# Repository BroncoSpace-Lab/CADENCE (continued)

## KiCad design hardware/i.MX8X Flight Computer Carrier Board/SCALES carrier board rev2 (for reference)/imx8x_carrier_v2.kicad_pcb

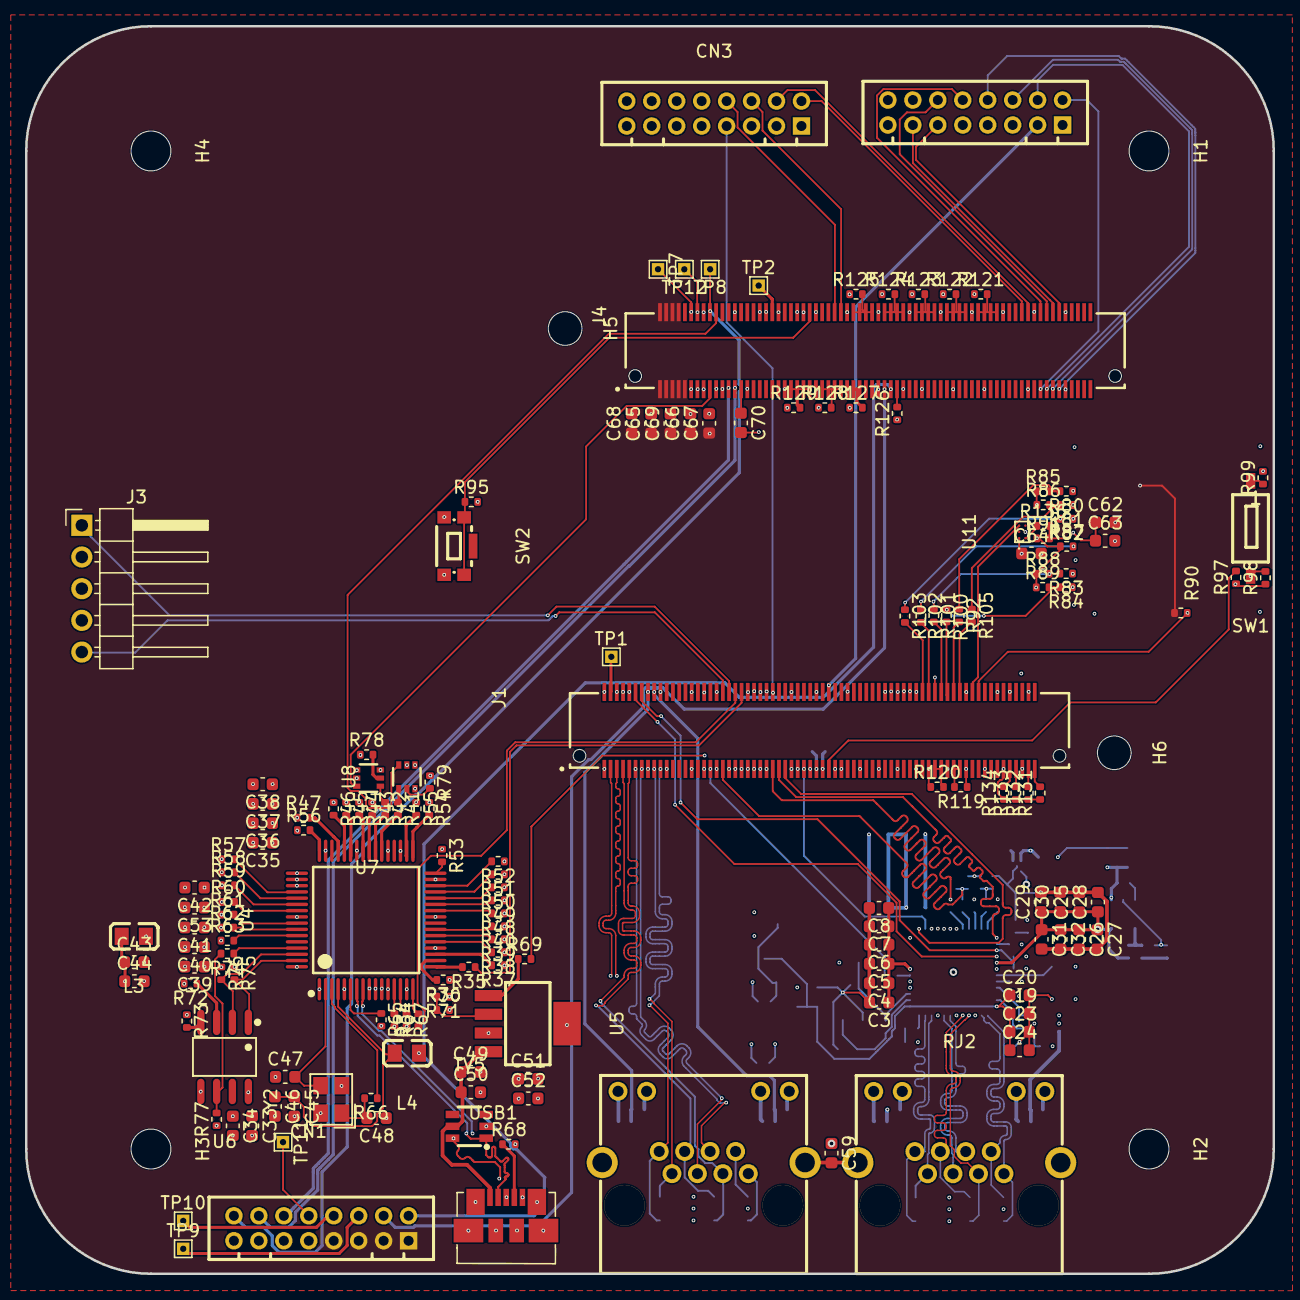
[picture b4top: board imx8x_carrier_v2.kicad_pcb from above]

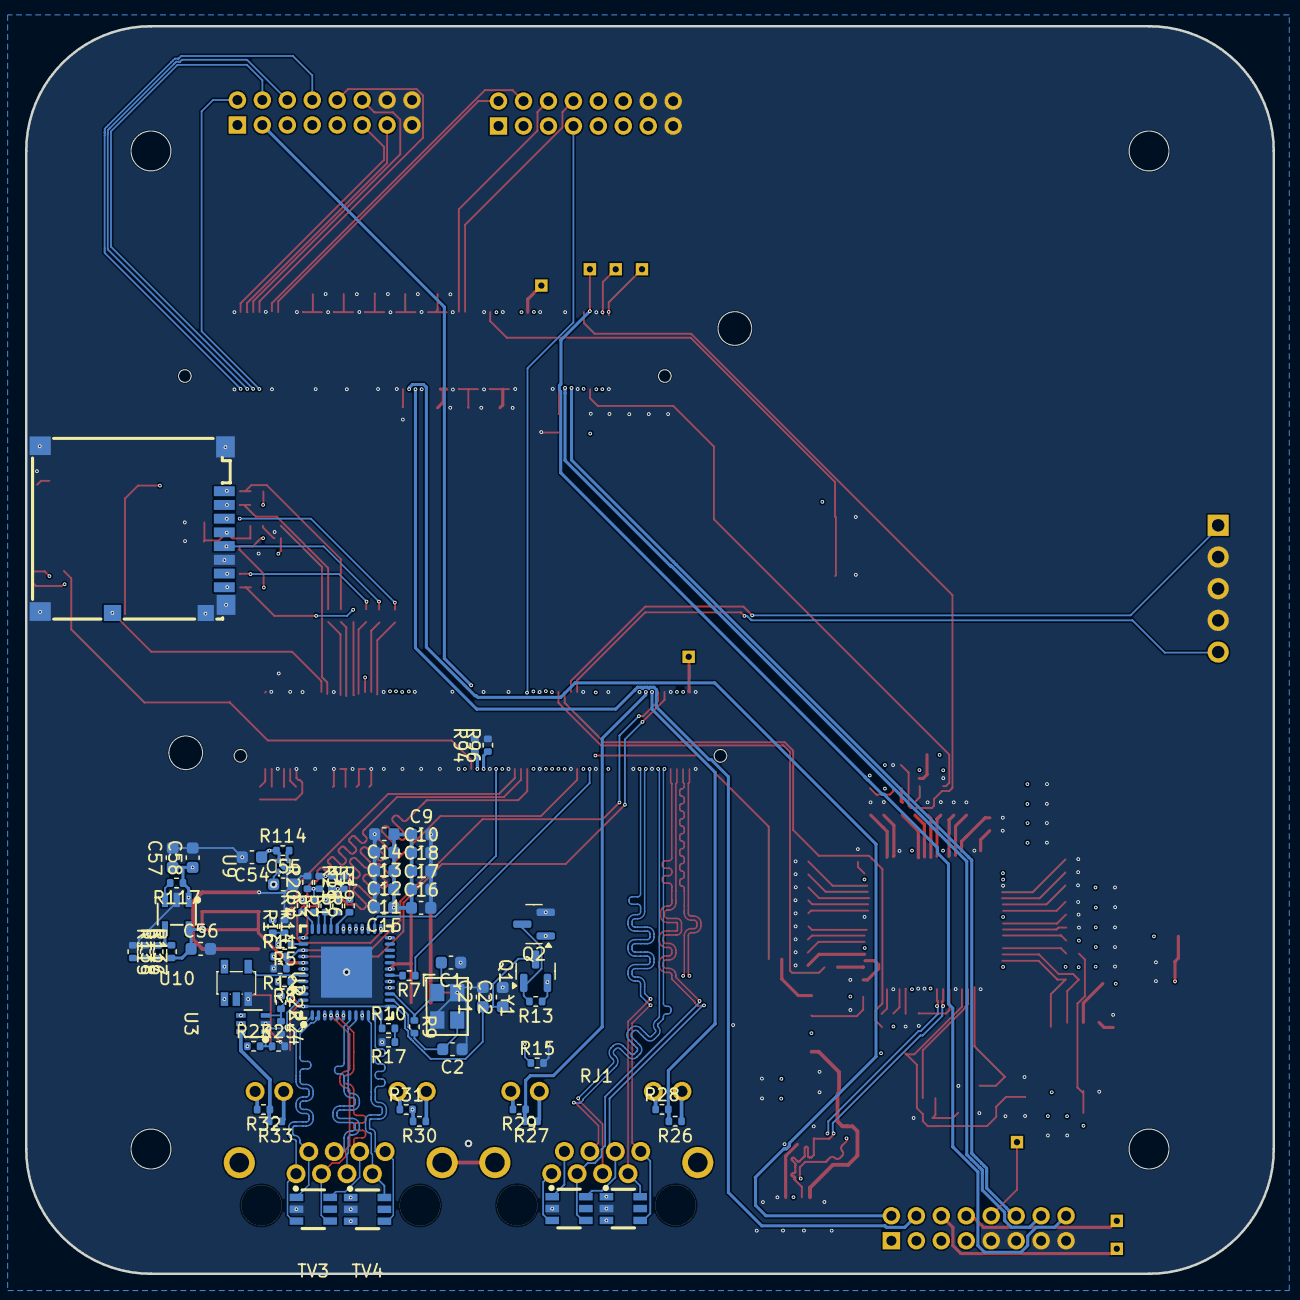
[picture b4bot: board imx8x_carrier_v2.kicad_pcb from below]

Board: 6 copper layers, 100.0 x 100.0 mm, 241 parts (73 on the bottom side), 215 nets.

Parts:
C1, C2: 18pF; C_0603_1608Metric
C3, C5, C12, C14, C15, C17, C19, C24, C25, C27, C32, C51: 1uF; C_0603_1608Metric
C4, C6, C11, C13, C16, C18, C20, C23, C26, C28, C31, C34, C35, C36, C37, C39, C40, C41, C42, C43, C46, C49, C52, C53, C54, C55, C57, C63, C64, C69: 100nF; C_0603_1608Metric
C7, C10, C21, C29, C59: 10nF; C_0603_1608Metric
C8, C9, C22, C30, C62: 10uF; C_0603_1608Metric
C33, C38, C44, C45, C56, C58, C67, C68: 4.7uF; C_0603_1608Metric
C47, C48: 12pF; C_0603_1608Metric
C50: 2.2uF; C_0603_1608Metric
C65, C66: 22uF; C_0603_1608Metric
C70: 220nF; C_0603_1608Metric
CN1, CN2, CN3: DF11-16DP-2DSA(08); CONN-TH_DF11-16DP-2DSA-08
Card1: 5027740891; TF-SMD_5027740891
H1, H2, H3, H4: MountingHole; MountingHole_3.2mm_M3
H5, H6: MountingHole; MountingHole_2.7mm_M2.5
J1, J4: BTH-070-02-L-D-A; SAMTEC_BTH-070-02-L-D-A
J3: Conn_01x05_Pin; PinHeader_1x05_P2.54mm_Horizontal
L3, L4: 600R/100MHz; L0805
Q1: IRLML6401; SOT-23
Q2: BSS138; SOT-23
R1, R2, R3, R4, R5, R29, R32, R34, R35, R41, R42, R80, R81, R82, R83, R84, R92, R100, R101, R102, R103, R105: 22; R_0402_1005Metric
R6, R68, R73, R91, R136: 0; R_0402_1005Metric
R7: 49.9; R_0402_1005Metric
R8, R74, R95: 2K; R_0402_1005Metric
R9: 1M; R_0402_1005Metric
R10, R63, R67: 1K; R_0402_1005Metric
R11, R14, R23: 5.76K; R_0402_1005Metric
R12, R16, R19, R20, R21, R24, R25, R27, R33: 2.49K; R_0402_1005Metric
R13, R15, R17, R18, R22, R26, R30, R36, R37, R38, R39, R40, R43, R44, R45, R46, R47, R48, R49, R50, R51, R52, R53, R54, R55, R56, R57, R58, R59, R60, R61, R62, R64, R69, R70, R72, R75, R76, R77, R78, R79: 10K; R_0402_1005Metric
R28, R31, R66: 200; R_0402_1005Metric
R65: 12K; R_0402_1005Metric
R71: 16.5K; R_0402_1005Metric
R85, R86, R87, R88, R89, R90: 49.9K; R_0402_1005Metric
R94, R96, R97, R98, R99, R137, R138: 1k; R_0402_1005Metric
R114, R117, R119, R120, R121, R122, R123, R124, R125, R126, R127, R128, R129, R131, R132, R133, R134: 10k; R_0402_1005Metric
R115: 2k; R_0402_1005Metric
R116: 13k; R_0402_1005Metric
RJ1, RJ2: RJHSE5384; RJ45-TH_RJHSE5384
SW1: SW_DIP_x01; SW-SMD_1.27-1P-TPPT
SW2: KMR221GLFS; KEY-SMD_KMR2XXGXXX
TP1, TP2, TP7, TP8, TP9, TP10, TP11, TP12: TestPoint; TestPoint_THTPad_1.0x1.0mm_Drill0.5mm
TV1, TV2, TV3, TV4, TV5: SRV05-4.TCT; SOT-23-6_L2.9-W1.6-P0.95-LS2.8-BR
U1: DP83867IRRGZR; VQFN-48_L7.0-W7.0-P0.50-BL-EP4.1
U2: 74AUP1G08; SOT-23-5_L3.0-W1.7-P0.95-LS2.8-BR
U3: 74LVC2G07; SOT-363_L2.1-W1.3-P0.65-LS2.2-BL
U4: FT2232HL; LQFP-64_L10.0-W10.0-P0.50-LS12.0-TL
U5: LP38693MP-ADJ/NOPB; SOT-223-5_L6.5-W3.5-P1.50-LS7.0-BL
U6: CAT93C66VI-GT3; SOIC-8_L4.9-W3.9-P1.27-LS6.0-BL
U7, U8: TXS0101DCKR; SC-70-6_L2.0-W1.3-P0.65-LS2.1-BR
U9: TLV71310PDQNR; X2SON-4_L1.0-W1.0-P0.65-TL-EP
U10: MCP1824T-ADJE/OT; SOT-23-5_L3.0-W1.7-P0.95-LS2.8-BL
U11: BD2204GUL-E2; BGA-6_L1.5-W1.0-P0.50_BD2204GUL-E2
USB1: 47346-0001; MICRO-USB-SMD_47346-0001
Y1: 25MHz; CRYSTAL-SMD_4P-L3.2-W2.5-BL-2
Y2: 12MHz; CRYSTAL-SMD_4P-L3.2-W2.5-BL

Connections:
1V8_FTDI: C35.1, C36.1, C37.1, C38.1, U4.12 (VCORE), U4.37 (VCORE), U4.49 (VREGOUT), U4.64 (VCORE)
3V3_FTDI: C33.1, C34.1, C39.1, C40.1, C41.1, C42.1, C51.1, C52.1, C53.1, L3.1, L4.1, R63.1, R67.2, R71.1, R75.1, R76.1, R77.1, U4.20 (VCCIO), U4.31 (VCCIO), U4.42 (VCCIO), U4.50 (VREGIN), U4.56 (VCCIO), U5.3 (OUT), U6.8 (VCC)
/Debug USB - UART/DEBUG_USB_DN: TV5.1, U4.7 (DM), USB1.2 (Data-)
/Debug USB - UART/DEBUG_USB_DP: TV5.6, U4.8 (DP), USB1.3 (Data+)
/Debug USB - UART/DEBUG_USB_ID: R68.1, USB1.4 (ID)
/Debug USB - UART/FTDI_OSCI: C47.2, U4.2 (OSCI), Y2.3
/Debug USB - UART/FTDI_OSCO: C48.2, R66.2, Y2.1
/Debug USB - UART/M40_UART0_RX: R41.1, U8.4 (B)
/Debug USB - UART/M40_UART0_TX: R42.1, U7.4 (B)
ETH1_A_TX_N: RJ2.2, TV3.1, U1.2 (TD_M_A)
ETH1_A_TX_P: RJ2.1, TV3.3, U1.1 (TD_P_A)
ETH1_B_TX_N: RJ2.6, TV3.6, U1.5 (TD_M_B)
ETH1_B_TX_P: RJ2.3, TV3.4, U1.4 (TD_P_B)
ETH1_C_TXCLK_N: RJ2.5, TV4.3, U1.8 (TD_M_C)
ETH1_C_TXCLK_P: RJ2.4, TV4.1, U1.7 (TD_P_C)
ETH1_D_RXDV_N: RJ2.8, TV4.4, U1.11 (TD_M_D)
ETH1_D_RXDV_P: RJ2.7, TV4.6, U1.10 (TD_P_D)
ETH1_LED0: R32.1, R33.2, U3.6 (1Y)
ETH1_LED1: R30.2, R31.2, U3.4 (2Y)
GND: C1.1, C2.1, C3.2, C4.2, C5.2, C6.2, C7.2, C8.2, C9.2, C10.2, C11.2, C12.2, C13.2, C14.2, C15.2, C16.2, C17.2, C18.2, C19.2, C20.2, C21.2, C22.2, C23.2, C24.2, C25.2, C26.2, C27.2, C28.2, C29.2, C30.2, C31.2, C32.2, C33.2, C34.2, C35.2, C36.2, C37.2, C38.2, C39.2, C40.2, C41.2, C42.2, C43.2, C44.2, C45.2, C46.2, C47.1, C48.1, C49.2, C50.2, C51.2, C52.2, C53.2, C54.2, C55.2, C56.2, C57.2, C58.2, C59.1, C62.2, C63.2, C64.2, C65.2, C66.2, C67.2, C68.2, C69.2, C70.2, CN1.9, CN1.11, CN1.13, CN1.15, CN2.14, CN2.15, CN2.16, CN3.14, CN3.15, CN3.16, Card1.6 (VSS), Card1.10 (DET), Card1.11 (SHELL), Card1.12 (SHELL), Card1.13 (SHELL), Card1.14 (SHELL), J1.03 (A2), J1.06 (B3), J1.09 (A5), J1.12 (B6), J1.13 (A7), J1.18 (B9), J1.23 (A12), J1.24 (B12), J1.30 (B15), J1.36 (B18), J1.39 (A20), J1.40 (B20), J1.46 (B23), J1.49 (A25), J1.52 (B26), J1.58 (B29), J1.61 (A31), J1.64 (B32), J1.71 (A36), J1.74 (B37), J1.79 (A40), J1.80 (B40), J1.89 (A45), J1.90 (B45), J1.100 (B50), J1.103 (A52), J1.108 (B54), J1.111 (A56), J1.120 (B60), J1.121 (A61), J1.126 (B63), J1.131 (A66), J1.139 (A70), J1.140 (B70), J3.2, J3.3, J3.4, J4.09 (C5), J4.10 (D5), J4.19 (C10), J4.22 (D11), J4.29 (C15), J4.36 (D18), J4.39 (C20), J4.46 (D23), J4.49 (C25), J4.56 (D28), J4.59 (C30), J4.62 (D31), J4.69 (C35), J4.70 (D35), J4.79 (C40), J4.80 (D40), J4.89 (C45), J4.90 (D45), J4.95 (C48), J4.100 (D50), J4.107 (C54), J4.112 (D56), J4.115 (C58), J4.120 (D60), J4.125 (C63), J4.130 (D65), Q2.2 (S), R12.2, R15.2, R16.2, R17.2, R20.2, R21.2, R24.2, R25.2, R36.1, R37.1, R38.1, R39.1, R40.1, R43.1, R44.1, R45.1, R46.1, R47.1, R48.1, R49.1, R50.1, R51.1, R52.1, R53.1, R54.1, R55.1, R56.1, R57.1, R58.1, R59.1, R60.1, R61.1, R62.1, R64.2, R65.2, R68.2, R70.2, R73.1, R94.2, R96.2, R99.2, R119.1, R120.1, R121.1, R122.1, R123.1, R124.1, R125.1, R126.1, R127.1, R128.1, R129.1, R131.1, R132.1, R133.1, R134.1, R137.1, R138.1, SW2.3, SW2.4, TV1.2, TV2.2, TV3.2, TV4.2, TV5.2, U1.49 (GND), U2.3 (GND), U3.2 (GND), U4.1 (GND), U4.5 (GND), U4.10 (AGND), U4.11 (GND), U4.15 (GND), U4.25 (GND), U4.35 (GND), U4.47 (GND), U4.51 (GND), U5.5 (GND), U6.5 (GND), U7.2 (GND), U8.2 (GND), U9.2 (GND), U9.5 (PAD), U10.2 (GND), U11.B2 (GND), USB1.5 (GND), USB1.6, Y1.2, Y1.4, Y2.2, Y2.4
GNDPWR: C59.2, RJ1.13 (SHELL), RJ1.14 (SHELL), RJ2.13 (SHELL), RJ2.14 (SHELL)
LED0_LINK: R23.2, R25.1, U1.47 (LED_0), U3.1 (1A)
LED2_ACT: R22.2, R24.1, U1.45 (LED_2), U3.3 (2A)
unnamed: CN1.6, TP9.1
unnamed: CN1.8, TP10.1
unnamed: CN1.10, TP11.1
unnamed: Card1.2 (CD/DAT3), R81.1
unnamed: Card1.3 (CMD), R82.1
unnamed: Card1.7 (DAT0), R83.1
unnamed: Card1.8 (DAT1), R84.1
unnamed: Card1.1 (DAT2), R80.1
unnamed: C62.1, C63.1, Card1.4 (VDD), R91.2, R136.2
unnamed: J1.25 (A13), R105.2
unnamed: J1.27 (A14), R92.2
unnamed: J1.29 (A15), R100.2
unnamed: J1.31 (A16), R101.2
unnamed: J1.35 (A18), R102.2
unnamed: J1.37 (A19), R103.2
unnamed: J1.02 (B1), R131.2
unnamed: J1.04 (B2), R132.2
unnamed: J1.08 (B4), R133.2
unnamed: J1.10 (B5), R134.2
unnamed: J1.26 (B13), J1.28 (B14), R119.2
unnamed: J1.32 (B16), J1.34 (B17), R120.2
unnamed: J4.31 (C16), J4.33 (C17), J4.35 (C18), J4.37 (C19), R121.2
unnamed: J4.41 (C21), J4.43 (C22), J4.45 (C23), J4.47 (C24), R122.2
unnamed: J4.51 (C26), J4.53 (C27), J4.55 (C28), J4.57 (C29), R123.2
unnamed: J4.61 (C31), J4.63 (C32), J4.65 (C33), J4.67 (C34), R124.2
unnamed: J4.71 (C36), J4.73 (C37), J4.75 (C38), J4.77 (C39), R125.2
unnamed: J4.64 (D32), R126.2
unnamed: J4.76 (D38), J4.78 (D39), R127.2
unnamed: J4.82 (D41), J4.84 (D42), J4.86 (D43), J4.88 (D44), R128.2
unnamed: J4.92 (D46), J4.94 (D47), J4.96 (D48), J4.98 (D49), R129.2
unnamed: C19.1, C20.1, C21.1, C22.1, C23.1, C24.1, Q1.3 (D), U1.13 (VDDA1P8), U1.48 (VDDA1P8)
unnamed: Q1.1 (G), Q2.3 (D), R13.2
unnamed: R10.2, R17.1
unnamed: R99.1, SW1.1
unnamed: R115.1, R137.2, R138.2
unnamed: R29.2, RJ1.9 (L-)
unnamed: R28.1, RJ1.11 (R-)
unnamed: R32.2, RJ2.9 (L-)
unnamed: R31.1, RJ2.11 (R-)
unnamed: R7.2, U1.18 (CLK_OUT)
unnamed: R10.1, U1.12 (RBIAS)
unnamed: U1.43 (RESET_N), U2.4 (Y)
unnamed: R6.1, U1.32 (RX_CLK)
unnamed: R5.1, U1.38 (RX_CTRL)
unnamed: R1.1, U1.33 (RX_D0)
unnamed: R2.1, U1.34 (RX_D1)
unnamed: R3.1, U1.35 (RX_D2)
unnamed: R4.1, U1.36 (RX_D3)
unnamed: C1.2, R9.1, U1.15 (X_I), Y1.1
unnamed: C2.2, R9.2, U1.14 (X_O), Y1.3
unnamed: R48.2, U4.26 (ACBUS0)
unnamed: R49.2, U4.27 (ACBUS1)
unnamed: R50.2, U4.28 (ACBUS2)
unnamed: R51.2, U4.29 (ACBUS3)
unnamed: R52.2, U4.30 (ACBUS4)
unnamed: R53.2, U4.32 (ACBUS5)
unnamed: R54.2, U4.33 (ACBUS6)
unnamed: R55.2, U4.34 (ACBUS7)
unnamed: R34.2, U4.16 (ADBUS0)
unnamed: R35.2, U4.17 (ADBUS1)
unnamed: R36.2, U4.18 (ADBUS2)
unnamed: R37.2, U4.19 (ADBUS3)
unnamed: R38.2, U4.21 (ADBUS4)
unnamed: R39.2, U4.22 (ADBUS5)
unnamed: R40.2, U4.23 (ADBUS6)
unnamed: R56.2, U4.48 (BCBUS0)
unnamed: R57.2, U4.52 (BCBUS1)
unnamed: R58.2, U4.53 (BCBUS2)
unnamed: R59.2, U4.54 (BCBUS3)
unnamed: R60.2, U4.55 (BCBUS4)
unnamed: R61.2, U4.57 (BCBUS5)
unnamed: R62.2, U4.58 (BCBUS6)
unnamed: R63.2, U4.59 (BCBUS7)
unnamed: R41.2, U4.38 (BDBUS0)
unnamed: R42.2, U4.39 (BDBUS1)
unnamed: R43.2, U4.40 (BDBUS2)
unnamed: R44.2, U4.41 (BDBUS3)
unnamed: R45.2, U4.43 (BDBUS4)
unnamed: R46.2, U4.44 (BDBUS5)
unnamed: R47.2, U4.45 (BDBUS6)
unnamed: R76.2, U4.62 (EECLK), U6.2 (SK)
unnamed: R75.2, U4.63 (EECS), U6.1 (CS)
unnamed: R74.1, U4.61 (EEDATA)
unnamed: R66.1, U4.3 (OSCO)
unnamed: R65.1, U4.6 (REF)
unnamed: R64.1, U4.13 (TEST)
unnamed: C45.1, C46.1, L4.2, U4.4 (VPHY)
unnamed: C43.1, C44.1, L3.2, U4.9 (VPLL)
unnamed: R67.1, U4.14 (~RESET)
unnamed: R70.1, R71.2, U5.2 (ADJ)
unnamed: R69.1, U5.1 (EN)
unnamed: R72.1, U6.3 (DI)
unnamed: R73.2, U6.4 (DO)
unnamed: R74.2, R77.2, U6.6 (ORG)
unnamed: R78.2, U7.5 (OE)
unnamed: R79.2, U8.5 (OE)
unnamed: R114.2, U9.3 (EN)
unnamed: R115.2, R116.2, U10.4 (ADJ)
unnamed: R117.2, U10.3 (EN)
SD1_SPWR: R136.1, U11.B1 (VOUT)
VBUS_DEBUG_USB: C49.1, C50.1, TV5.5, U5.4 (IN), USB1.1 (VBUS)
VCC_1V8_OUT: C54.1, J4.127 (C64), R11.1, R14.1, R18.1, R19.1, R22.1, R23.1, R78.1, R79.1, R114.1, TP12.1, U2.5 (VCC), U3.5 (VCC), U7.1 (VCCA), U8.1 (VCCA), U9.4 (IN)
VCC_3V3: C65.1, C66.1, C67.1, C68.1, C69.1, CN1.1, CN1.3, CN1.5, CN1.7, J4.132 (D66), J4.133 (C67), J4.134 (D67), J4.135 (C68), J4.136 (D68), J4.137 (C69), J4.138 (D69), J4.139 (C70), J4.140 (D70), R90.1
VCC_3V3_OUT: C57.1, C58.1, C64.1, J4.129 (C65), R8.2, R26.1, R27.1, R30.1, R33.1, R72.2, R95.2, R117.1, RJ1.10 (L+), RJ1.12 (R+), RJ2.10 (L+), RJ2.12 (R+), TP7.1, U7.6 (VCCB), U8.6 (VCCB), U10.1 (VIN), U11.A1 (VIN1)
VCC_ENET_2V5: C3.1, C4.1, C5.1, C6.1, C7.1, C8.1, C25.1, C26.1, C27.1, C28.1, C29.1, C30.1, C31.1, C32.1, C56.1, Q2.1 (G), R15.1, R116.1, U1.3 (VDDA2P5), U1.9 (VDDA2P5), U1.19 (VDDIO), U1.30 (VDDIO), U1.41 (VDDIO), U10.5 (OUT)
VCC_LDO_SD1: J1.33 (A17), R85.1, R86.1, R87.1, R88.1, R89.1, R91.1
VCC_SCU_1V8: J4.93 (C47), R97.1, R98.1
VDD_ADC_1V8: C70.1, J4.114 (D57)
VDD_ETH_1V0: C9.1, C10.1, C11.1, C12.1, C13.1, C14.1, C15.1, C16.1, C17.1, C18.1, C55.1, Q1.2 (S), R13.1, U1.6 (VDD1P0), U1.24 (VDD1P0), U1.31 (VDD1P0), U1.42 (VDD1P0), U9.1 (OUT)
X_ADMA_I2C0_SCL: CN1.2, J4.66 (D33)
X_ADMA_I2C0_SDA: CN1.4, J4.68 (D34)
X_ADMA_I2C3_SCL: CN3.10, J1.112 (B56)
X_ADMA_I2C3_SDA: CN3.12, J1.107 (A54)
X_ADMA_SPI2_CS0: CN2.1, J1.41 (A21)
X_ADMA_SPI2_CS1: CN2.3, J1.67 (A34)
X_ADMA_SPI2_SCK: CN2.5, J1.43 (A22)
X_ADMA_SPI2_SDI: CN2.7, J1.45 (A23)
X_ADMA_SPI2_SDO: CN2.9, J1.47 (A24)
X_ADMA_UART0_RX: J1.97 (A49), R34.1
X_ADMA_UART0_TX: J1.95 (A48), R35.1
X_ADMA_UART2_RX: J1.99 (A50), J3.1
X_ADMA_UART2_TX: J1.101 (A51), J3.5
X_BOOT_MODE0: J1.66 (B33), R98.2, SW1.2
X_BOOT_MODE1: J1.68 (B34), R97.2
X_BOOT_MODE2: J1.70 (B35), R94.1
X_BOOT_MODE3: J1.72 (B36), R96.1
X_CONN_ENET1_REFCLK: J1.106 (B53), R7.1
X_CONN_ENET1_RXC: J1.86 (B43), R6.2
X_CONN_ENET1_RXD0: J1.102 (B51), R1.2, R19.2, R21.1
X_CONN_ENET1_RXD1: J1.94 (B47), R2.2
X_CONN_ENET1_RXD2: J1.92 (B46), R3.2, R18.2, R20.1
X_CONN_ENET1_RXD3: J1.88 (B44), R4.2
X_CONN_ENET1_RX_CTL: J1.104 (B52), R5.2
X_CONN_ENET1_RX_CTRL: R14.2, R16.1
X_CONN_ENET1_TXC: J1.78 (B39), U1.29 (GTX_CLK)
X_CONN_ENET1_TXD0: J1.96 (B48), U1.28 (TX_D0)
X_CONN_ENET1_TXD1: J1.98 (B49), U1.27 (TX_D1)
X_CONN_ENET1_TXD2: J1.76 (B38), U1.26 (TX_D2)
X_CONN_ENET1_TXD3: J1.82 (B41), U1.25 (TX_D3)
X_CONN_ENET1_TX_CTL: J1.84 (B42), U1.37 (TX_CTRL)
X_CONN_ETH0_MDC: J1.135 (A68), U1.16 (MDC)
X_CONN_ETH0_MDIO: J1.133 (A67), U1.17 (MDIO)
X_CONN_ETH1_PHY_INT: R8.1, U1.44 (INT/PWDN)
X_CONN_USDHC1_CD_B: Card1.9 (SW), J1.19 (A10), R90.2
X_CONN_USDHC1_CLK: Card1.5 (CLK), R87.2, R102.1
X_CONN_USDHC1_CMD: R82.2, R103.1
X_CONN_USDHC1_DATA0: R83.2, R88.2, R101.1
X_CONN_USDHC1_DATA1: R84.2, R89.2, R100.1
X_CONN_USDHC1_DATA2: R80.2, R85.2, R92.1
X_CONN_USDHC1_DATA3: R81.2, R86.2, R105.1
X_CONN_USDHC1_RESET_B: J1.21 (A11), U11.A3 (EN)
X_ETH0_A_TX_N: J1.136 (B68), RJ1.2, TV1.1
X_ETH0_A_TX_P: J1.138 (B69), RJ1.1, TV1.3
X_ETH0_B_TX_N: J1.132 (B66), RJ1.6, TV1.6
X_ETH0_B_TX_P: J1.134 (B67), RJ1.3, TV1.4
X_ETH0_C_TXCLK_N: J1.128 (B64), RJ1.5, TV2.3
X_ETH0_C_TXCLK_P: J1.130 (B65), RJ1.4, TV2.1
X_ETH0_D_RXDV_N: J1.122 (B61), RJ1.8, TV2.4
X_ETH0_D_RXDV_P: J1.124 (B62), RJ1.7, TV2.6
X_ETH0_INT: J1.137 (A69), TP1.1
X_ETH0_LED0: J1.123 (A62), R27.2, R29.1
X_ETH0_LED1: J1.125 (A63), R26.2, R28.2
X_ETH_GPIO0: J1.127 (A64), R11.2, R12.1, U1.39 (GPIO_0)
X_ETH_GPIO1: J1.129 (A65), U1.40 (GPIO_1)
X_LSIO_GPIO1_IO09: CN1.14, J4.116 (D58)
X_LSIO_GPIO1_IO10: CN1.12, J4.118 (D59)
X_LSIO_GPIO1_IO12: CN3.1, J4.126 (D63)
X_LSIO_GPIO1_IO13: CN3.3, J4.128 (D64)
X_LSIO_GPIO1_IO14: CN3.5, J4.122 (D61)
X_LSIO_GPIO1_IO25: CN3.2, J4.23 (C12)
X_LSIO_GPIO1_IO26: CN3.4, J4.21 (C11)
X_LSIO_GPIO1_IO29: CN3.6, J4.81 (C41)
X_LSIO_GPIO1_IO30: CN3.8, J4.83 (C42)
X_LSIO_QSPI0B_DATA0: CN2.8, J4.12 (D6)
X_LSIO_QSPI0B_DATA1: CN2.6, J4.14 (D7)
X_LSIO_QSPI0B_DATA2: CN2.4, J4.16 (D8)
X_LSIO_QSPI0B_DATA3: CN2.2, J4.18 (D9)
X_LSIO_QSPI0B_DQS: CN2.10, J4.17 (C9)
X_LSIO_QSPI0B_SCLK: CN2.12, J4.15 (C8)
X_LSIO_QSPIOB_SS0_B: CN2.11, J4.11 (C6)
X_LSIO_QSPIOB_SS1_B: CN2.13, J4.13 (C7)
X_LSO_GPIO1_IO17: CN3.7, J1.85 (A43)
X_LSO_GPIO1_IO18: CN3.9, J1.87 (A44)
X_LSO_GPIO1_IO19: CN3.11, J1.93 (A47)
X_LSO_GPIO1_IO20: CN3.13, J1.91 (A46)
X_M40_UART0_RX: J4.121 (C61), U8.3 (A)
X_M40_UART0_TX: J4.124 (D62), U7.3 (A)
X_PGOOD: J4.105 (C53), R69.2
X_POR_B_1V8: J4.101 (C51), U2.1 (A)
X_POR_B_3V3: J4.103 (C52), TP2.1
X_SCU_WDOG0_WDOG_OUT: CN1.16, J4.123 (C62), TP8.1
~X_nRESET_IN: J4.91 (C46), R95.1, SW2.1, SW2.2

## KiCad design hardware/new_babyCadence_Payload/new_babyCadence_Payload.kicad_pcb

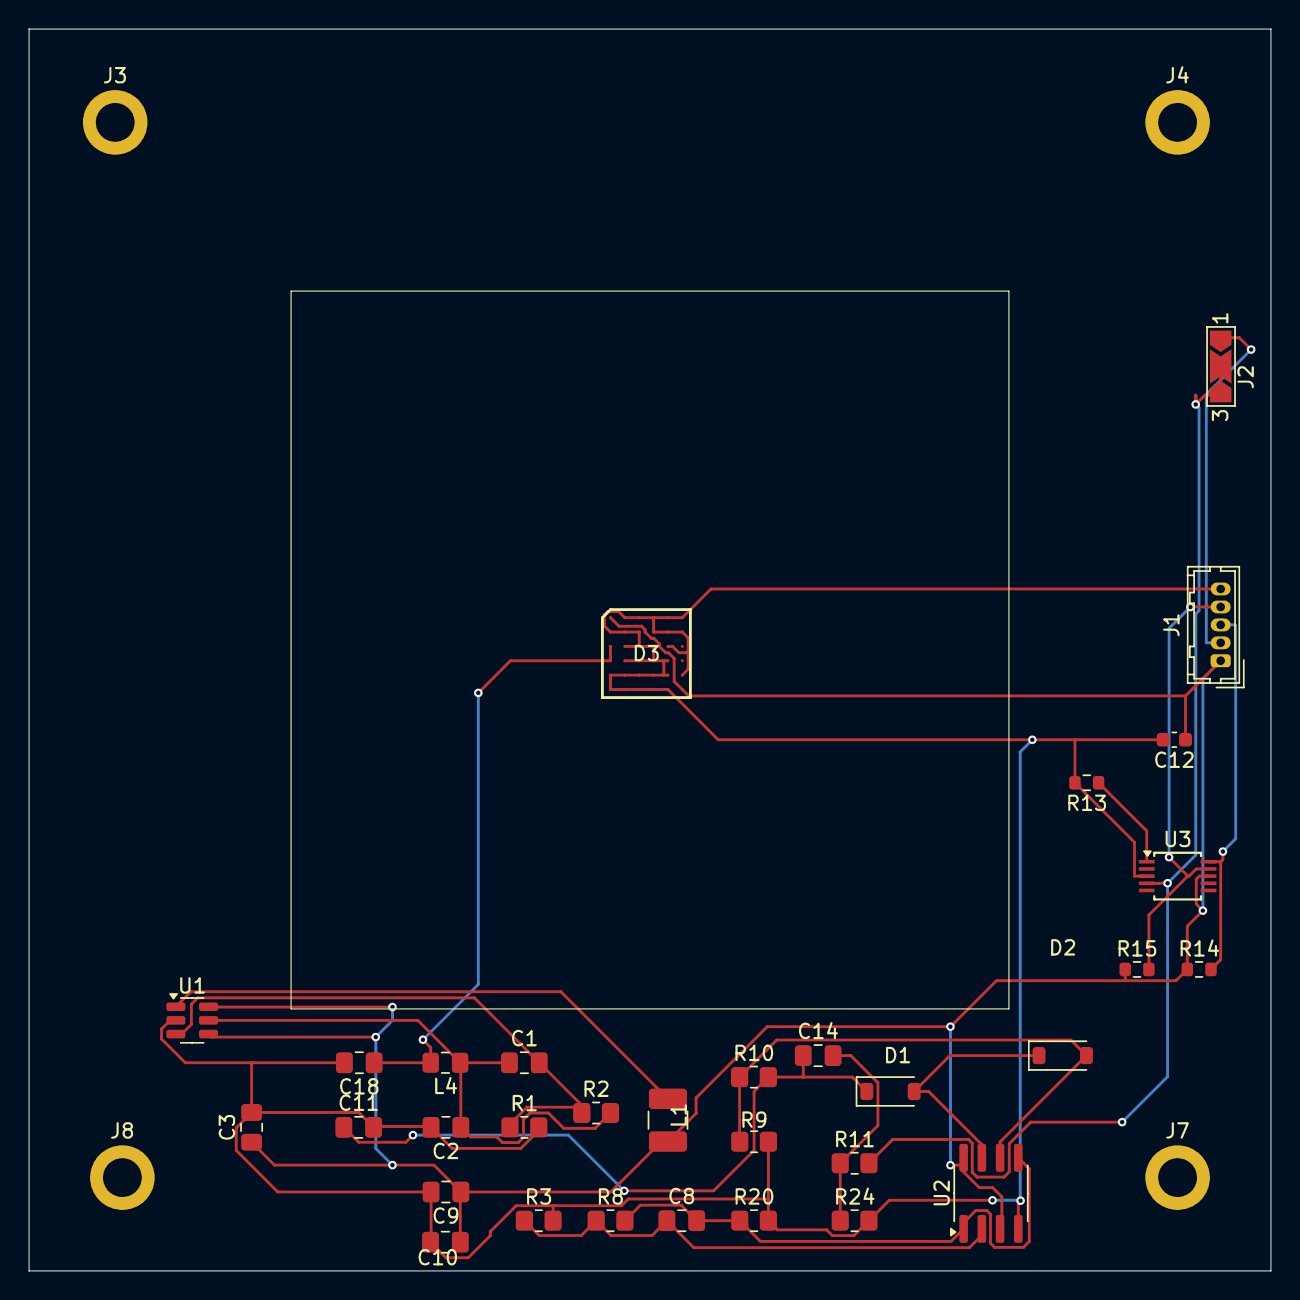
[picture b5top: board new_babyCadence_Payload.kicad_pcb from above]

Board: 2 copper layers, 86.5 x 86.5 mm, 36 parts (0 on the bottom side), 17 nets.

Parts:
C1: 22pF; C_0805_2012Metric_Pad1.18x1.45mm_HandSolder
C2: 0.47pF; C_0805_2012Metric_Pad1.18x1.45mm_HandSolder
C3, C18: 1uF; C_0805_2012Metric_Pad1.18x1.45mm_HandSolder
C8: 10pF; C_0805_2012Metric_Pad1.18x1.45mm_HandSolder
C9: 10uF; C_0805_2012Metric_Pad1.18x1.45mm_HandSolder
C10: 0.1uF; C_0805_2012Metric_Pad1.18x1.45mm_HandSolder
C11: 20nF; C_0805_2012Metric_Pad1.18x1.45mm_HandSolder
C12: 0.1; C_0603_1608Metric
C14: 0F; C_0805_2012Metric_Pad1.18x1.45mm_HandSolder
D1, D2: 40V 500mA; D_SOD-123
D3: MICROFJ-60035-TSV-TR1; BGA36C100P6X6_613X613X67
J1: Conn_01x05_Female; Hirose_DF13-05P-1.25DSA_1x05_P1.25mm_Vertical
J2: Conn_01x03_Socket; SolderJumper-3_P2.0mm_Open_TrianglePad1.0x1.5mm_NumberLabels
J3, J4, J7, J8: Conn_01x01_Pin; MountingHole_2.7mm_M2.5_ISO7380_Pad
L1: 47uH; L_1210_3225Metric_Pad1.42x2.65mm_HandSolder
L4: 2.5k Ohms; L_0805_2012Metric_Pad1.15x1.40mm_HandSolder
R1, R8, R20: 10k; R_0805_2012Metric_Pad1.20x1.40mm_HandSolder
R2: 226k; R_0805_2012Metric_Pad1.20x1.40mm_HandSolder
R3: 249; R_0805_2012Metric_Pad1.20x1.40mm_HandSolder
R9, R10: 100k; R_0805_2012Metric_Pad1.20x1.40mm_HandSolder
R11: 0k; R_0805_2012Metric_Pad1.20x1.40mm_HandSolder
R13, R14, R15: 10K; R_0603_1608Metric
R24: 24.9k; R_0805_2012Metric_Pad1.20x1.40mm_HandSolder
U1: LT3461ES6#TRPBF; TSOT-23-6
U2: LT1807IS8#PBF; SOIC-8_3.9x4.9mm_P1.27mm
U3: ADS1115IDGS; TSSOP-10_3x3mm_P0.5mm

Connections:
+5V: C3.1, C9.1, C10.1, C12.1, D3.A1 (CATHODE_1), D3.F6 (CATHODE_2), J1.1, L1.2, R14.1, R15.1, U1.4 (SHDN), U1.6 (Vin), U2.3 (+IN_A), U2.8 (V+), U3.8 (VDD)
/AMP OUT: J2.2, J2.3, R11.2, U3.4 (AIN0)
/Anode OUT: C18.1, D3.C1 (ANODE_1), D3.D1 (ANODE_2), L4.2
ADC0: J1.2, J2.1
GND: C2.2, C3.2, C9.2, C10.2, C11.2, C12.2, C18.2, D3.A2 (NC_1), D3.A3 (NC_2), D3.A4 (NC_3), D3.A5 (NC_4), D3.A6 (NC_5), D3.B1 (NC_6), D3.B2 (NC_7), D3.B3 (NC_8), D3.B4 (NC_9), D3.B5 (NC_10), D3.B6 (NC_11), D3.C2 (NC_12), D3.C3 (NC_13), D3.C4 (NC_14), D3.C5 (NC_15), D3.D2 (NC_16), D3.D3 (NC_17), D3.D4 (NC_18), D3.D5 (NC_19), D3.E1 (NC_20), D3.E2 (NC_21), D3.E3 (NC_22), D3.E4 (NC_23), D3.E5 (NC_24), D3.E6 (NC_25), D3.F1 (NC_26), D3.F2 (NC_27), D3.F3 (NC_28), D3.F4 (NC_29), D3.F5 (NC_30), J1.5, R1.2, R3.2, R9.2, R13.2, R20.2, R24.2, U1.2 (gnd), U2.4 (V-), U3.3 (GND)
unnamed: C14.2, R11.1, R24.1
unnamed: D1.2 (A), D2.1 (K), U2.7 (OUT_B)
unnamed: C11.1, C14.1, D1.1 (K), R10.2
unnamed: D2.2 (A), R9.1, R10.1, U2.6 (-IN_B)
unnamed: J1.3, R14.2, U3.10 (SCL)
unnamed: J1.4, R15.2, U3.9 (SDA)
unnamed: C1.2, R1.1, R2.1, U1.3 (FB)
unnamed: C1.1, C2.1, L4.1, R2.2, U1.5 (Vout)
unnamed: L1.1, U1.1 (sw)
unnamed: C8.2, R8.2, R20.1, U2.1 (OUT_A), U2.5 (+IN_B)
unnamed: C8.1, R3.1, R8.1, U2.2 (-IN_A)
unnamed: R13.1, U3.1 (ADDR)

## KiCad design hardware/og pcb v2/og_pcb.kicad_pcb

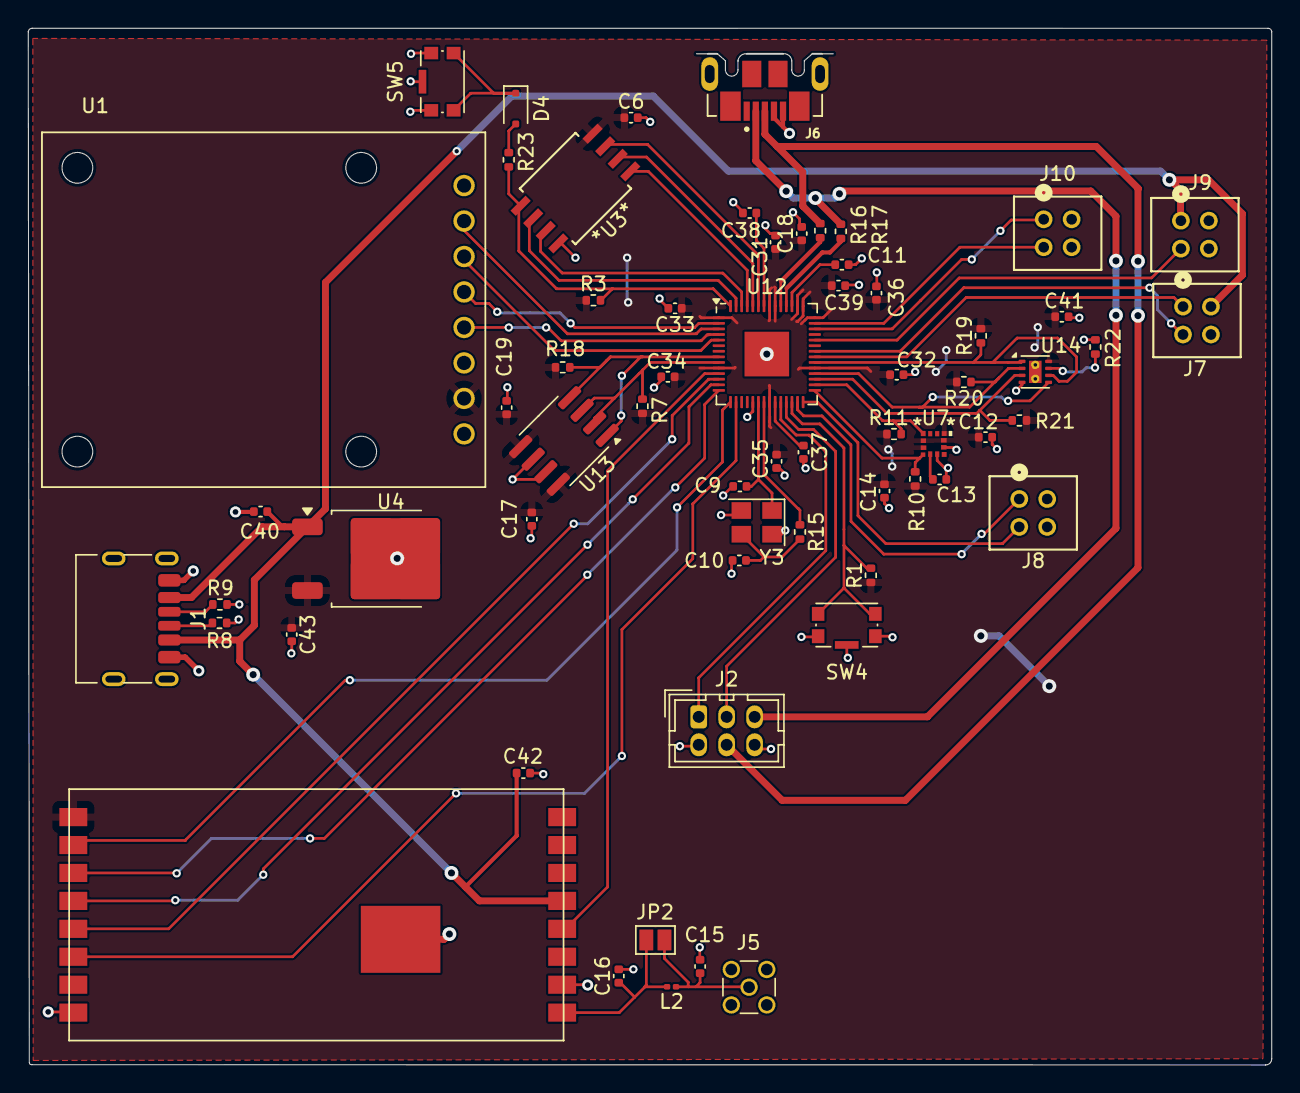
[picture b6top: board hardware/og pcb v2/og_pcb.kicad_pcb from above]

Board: 2 copper layers, 89.0 x 74.2 mm, 63 parts (0 on the bottom side), 52 nets.

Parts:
C6, C18, C31, C32, C33, C34, C35, C36, C37, C38, C42: 100n; C_0402_1005Metric
C9, C10: 15p; C_0402_1005Metric
C11, C39: 1u; C_0402_1005Metric
C12, C14, C17, C19: 100nF; C_0402_1005Metric
C13: 220nF; C_0402_1005Metric
C15, C16: DNP; C_0402_1005Metric
C40, C43: 10u; C_0402_1005Metric
C41: 0.01uF; C_0402_1005Metric
D4: NSR0320; D_SOD-323F
J1: USB_C_Receptacle_PowerOnly_6P; USB_C_Receptacle_HRO_TYPE-C-31-M-17
J2: Conn_02x03_Top_Bottom; Hirose_DF11-6DP-2DSA_2x03_P2.00mm_Vertical
J5: Conn_Coaxial; MMCX_Molex_73415-1471_Vertical
J6: USB_B_Micro; microUSB
J7, J8, J9, J10: Conn_02x02_Top_Bottom; CON4_2X2_UF_DF11_HIR
JP2: SolderJumper_2_Open; SolderJumper-2_P1.3mm_Open_Pad1.0x1.5mm
L2: DNP; L_0201_0603Metric
R1, R3, R7, R10, R11, R18: 10k; R_0402_1005Metric
R8, R9: 5.1k; R_0402_1005Metric
R15, R23: 1k; R_0402_1005Metric
R16, R17: 27; R_0402_1005Metric
R19, R20, R21, R22: 5k; R_0402_1005Metric
SW4, SW5: SW_Push_Shielded; SW_Push_1P1T-SH_NO_CK_KMR2xxG
U1: 254; MODULE_254
U3: W25Q128JVS; SOIC_208MIL_WIN
U4: BD33FC0FP; TO-252-2
U7: LSM303AGRTR; SON_03AGRTR_STM-L
U12: RP2040; QFN-56-1EP_7x7mm_P0.4mm_EP3.2x3.2mm
U13: INA219AxD; SOIC-8_3.9x4.9mm_P1.27mm
U14: TMP1075DSG; WSON-8-1EP_2x2mm_P0.5mm_EP0.9x1.6mm_ThermalVias
U16: RFM98PW
Y3: ABM8-272-T3; Crystal_SMD_3225-4Pin_3.2x2.5mm

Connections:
+1V1: C11.1, C37.1, C38.1, U12.23 (DVDD), U12.45 (VREG_VOUT), U12.50 (DVDD)
+3.3V: C6.1, C12.1, C14.1, C17.1, C18.1, C19.1, C31.1, C32.1, C33.1, C34.1, C35.1, C36.1, C39.1, C41.2, C43.1, R1.1, R3.1, R7.1, R10.1, R11.1, R18.1, R19.2, R20.2, R21.2, U1.7 (3V), U3.8 (VCC), U4.3 (VO), U7.2 (CS_XL), U7.3 (CS_MAG), U7.9 (Vdd), U7.10 (Vdd_I/O), U12.1 (IOVDD), U12.10 (IOVDD), U12.22 (IOVDD), U12.33 (IOVDD), U12.42 (IOVDD), U12.43 (ADC_AVDD), U12.44 (VREG_IN), U12.48 (USB_VDD), U12.49 (IOVDD), U13.5 (VS), U13.8 (IN+), U14.8 (V+), U16.9 (3.3V)
/RP2040 MCU/Crystal In: C9.1, U12.20 (XIN), Y3.1
/RP2040 MCU/Crystal Out: R15.1, U12.21 (XOUT)
/RP2040 MCU/QSPI_SCLK: U3.6 (CLK), U12.52 (QSPI_SCLK)
/RP2040 MCU/QSPI_SD0: U3.5 (DI(IO0)), U12.53 (QSPI_SD0)
/RP2040 MCU/QSPI_SD1: U3.2 (DO(IO1)), U12.55 (QSPI_SD1)
/RP2040 MCU/QSPI_SD2: U3.3 (IO2), U12.54 (QSPI_SD2)
/RP2040 MCU/QSPI_SD3: U3.7 (IO3), U12.51 (QSPI_SD3)
/RP2040 MCU/QSPI_SS: R3.2, R23.1, U3.1 (~CS), U12.56 (QSPI_SS)
Cosmic1 SDA: J7.1, U12.35 (GPIO23)
Cosmic2 SCL: J7.2, U12.36 (GPIO24)
Cosmic Analog: J9.2, U12.38 (GPIO26_ADC0)
Cosmic Ground: C6.2, C9.2, C10.2, C11.2, C12.2, C13.2, C14.2, C15.2, C16.2, C17.2, C18.2, C19.2, C31.2, C32.2, C33.2, C34.2, C35.2, C36.2, C37.2, C38.2, C39.2, C40.2, C41.1, C42.1, C43.2, J1.A12 (GND), J1.B12 (GND), J1.S1 (SHIELD), J2.2, J2.6, J5.2 (Ext), J6.4 (ID), J6.5 (GND), J7.4, J8.3, J8.4, J9.3, J9.4, J10.3, J10.4, R8.2, R9.2, R22.2, SW4.1, SW4.SH (B), SW5.1, SW5.SH (B), U1.6 (GND), U3.4 (GND), U4.2 (GND), U7.6 (GND), U7.8 (GND), U12.19 (TESTEN), U12.57 (GND), U13.6 (GND), U13.7 (IN-), U14.4 (GND), U14.9 (EP), U16.2 (GND), U16.16 (GND), U16.17 (GND), Y3.2, Y3.4
Cosmic Power: C40.1, C42.2, J1.A9 (VBUS), J1.B9 (VBUS), J7.3, J9.1, U4.1 (VCC), U16.5 (VCC(5V))
IMU SCL/SPC: R11.2, U7.1 (SCL/SPC), U12.30 (GPIO19)
IMU SDA/SDI/SCO: R10.2, U7.4 (SDA/SDI/SCO), U12.29 (GPIO18)
MicroSD CS: U1.2 (CS), U12.3 (GPIO1)
MicroSD Clock: U1.5 (CLK), U12.4 (GPIO2)
MicroSD MISO: U1.4 (DO), U12.2 (GPIO0)
MicroSD MOSI: U1.3 (DI), U12.5 (GPIO3)
unnamed: C10.1, R15.2, Y3.3
unnamed: D4.2 (A), R23.2
unnamed: D4.1 (K), SW5.2
unnamed: J1.A5 (CC1), R9.1
unnamed: J1.B5 (CC2), R8.1
unnamed: C15.1, J5.1 (In), JP2.1 (A), L2.1
unnamed: C16.1, JP2.2 (B), L2.2, U16.1 (ANT)
unnamed: C13.1, U7.5 (C1)
unnamed: R17.2, U12.46 (USB_DM)
unnamed: R16.2, U12.47 (USB_DP)
unnamed: R22.1, U14.7 (A0)
Power Monitor SCL: R18.2, U12.8 (GPIO6), U13.1 (A1), U13.4 (SCL)
Power Monitor SDA: R7.2, U12.9 (GPIO7), U13.2 (A0), U13.3 (SDA)
RF DIO4: U12.11 (GPIO8), U16.4 (DI/O4)
RF MISO: U12.15 (GPIO12), U16.10 (MISO)
RF MOSI: U12.14 (GPIO11), U16.11 (MOSI)
RF NSS: U12.12 (GPIO9), U16.13 (NSS)
RF Reset: U12.16 (GPIO13), U16.14 (RESET)
RF SCK: U12.13 (GPIO10), U16.12 (SCK)
SCL General: J8.2, U12.28 (GPIO17)
SDA General: J8.1, U12.27 (GPIO16)
SWCLK: J2.1, U12.24 (SWCLK)
SWD: J2.3, U12.25 (SWD)
Temp Alert: R21.1, U12.31 (GPIO20), U14.3 (ALERT)
Temp SCL: R20.1, U12.32 (GPIO21), U14.2 (SCL), U14.5 (A2)
Temp SDA: R19.1, U12.34 (GPIO22), U14.1 (SDA), U14.6 (A1)
UART Rx: J10.2, U12.41 (GPIO29_ADC3)
UART Tx: J10.1, U12.40 (GPIO28_ADC2)
USB_DM: J2.5, J6.2 (D-), R17.1
USB_DP: J2.4, J6.3 (D+), R16.1
WDO: R1.2, SW4.2, U12.26 (RUN)

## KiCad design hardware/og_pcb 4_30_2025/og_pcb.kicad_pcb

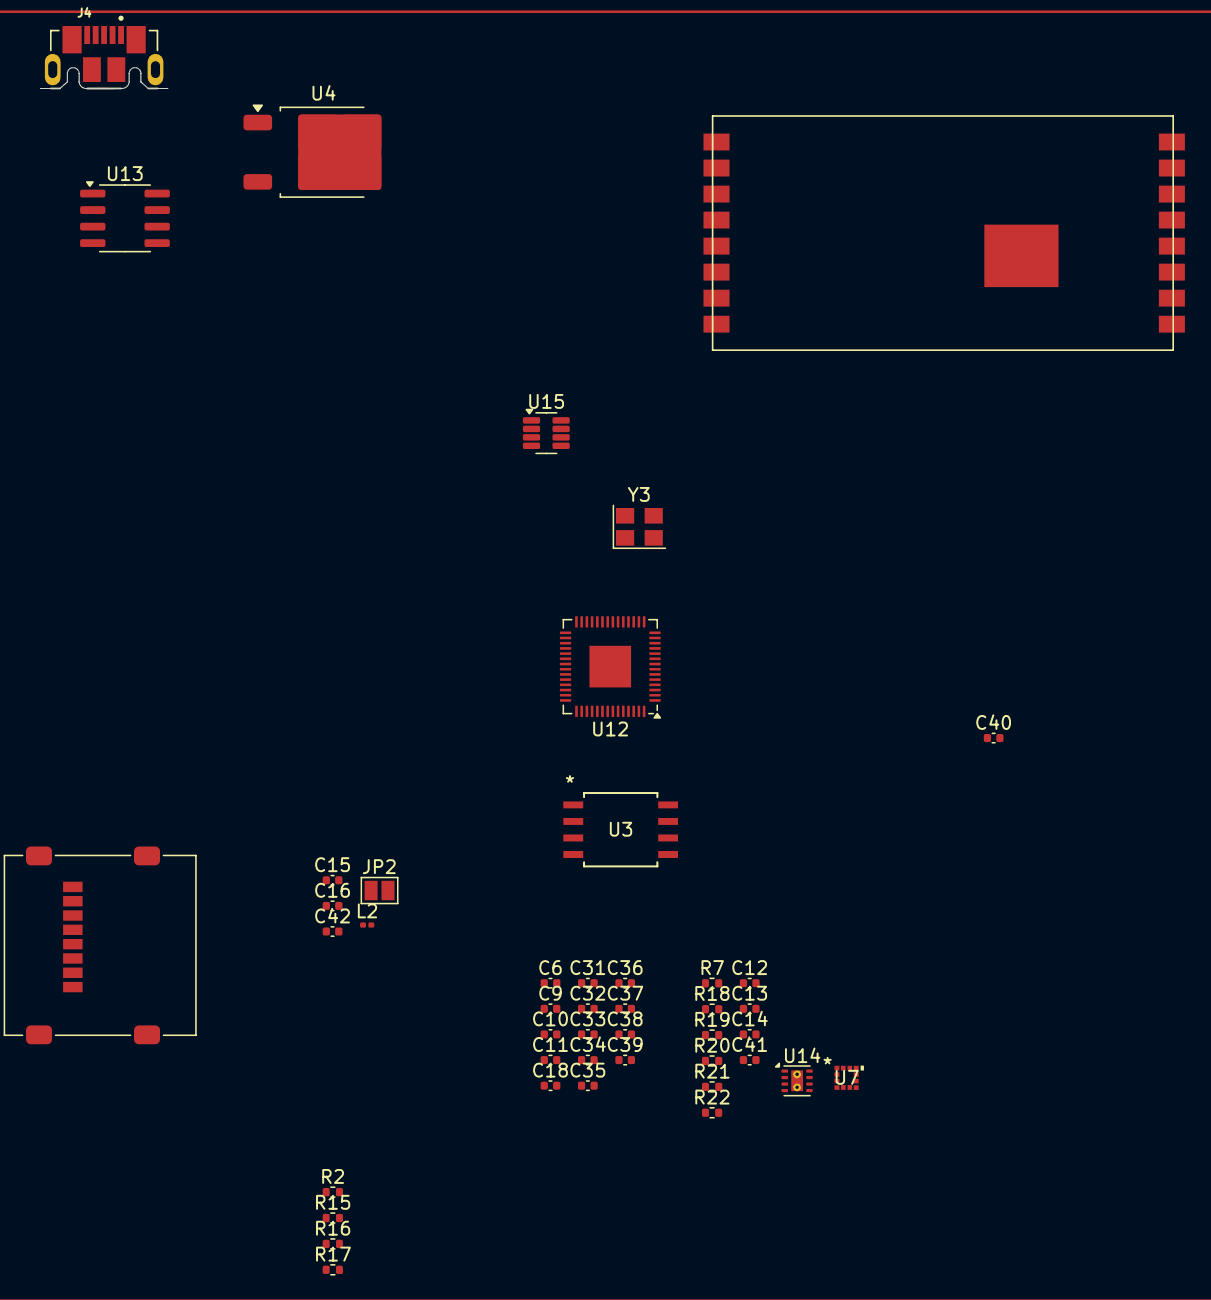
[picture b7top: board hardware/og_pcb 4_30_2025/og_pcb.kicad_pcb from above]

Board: 2 copper layers, 45 parts (0 on the bottom side), 41 nets, no tracks yet.

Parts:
C6, C18, C31, C32, C33, C34, C35, C36, C37, C38, C42: 100n; C_0402_1005Metric
C9, C10: 15p; C_0402_1005Metric
C11, C39: 1u; C_0402_1005Metric
C12, C14: 100nF; C_0402_1005Metric
C13: 220nF; C_0402_1005Metric
C15, C16: DNP; C_0402_1005Metric
C40: 10n; C_0402_1005Metric
C41: 0.01uF; C_0402_1005Metric
J4: USB_B_Micro; microUSB
J6: Micro_SD_Card; microSD_HC_Molex_47219-2001
JP2: SolderJumper_2_Open; SolderJumper-2_P1.3mm_Open_Pad1.0x1.5mm
L2: DNP; L_0201_0603Metric
R2, R7, R18: 10k; R_0402_1005Metric
R15: 1k; R_0402_1005Metric
R16, R17: 27; R_0402_1005Metric
R19, R20, R21, R22: 5k; R_0402_1005Metric
U3: W25Q128JVS; SOIC_208MIL_WIN
U4: BD33FC0FP; TO-252-2
U7: LSM303AGRTR; SON_03AGRTR_STM-L
U12: RP2040; QFN-56-1EP_7x7mm_P0.4mm_EP3.2x3.2mm
U13: INA219AxD; SOIC-8_3.9x4.9mm_P1.27mm
U14: TMP1075DSG; WSON-8-1EP_2x2mm_P0.5mm_EP0.9x1.6mm_ThermalVias
U15: MAX6369; SOT-23-8
U16: RFM98PW
Y3: ABM8-272-T3; Crystal_SMD_3225-4Pin_3.2x2.5mm

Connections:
+1V1: C11.1, C37.1, C38.1, U12.23 (DVDD), U12.45 (VREG_VOUT), U12.50 (DVDD)
+5V: C40.1, C42.2, J4.1 (VBUS), U4.1 (VCC), U16.5 (VCC(5V))
/RP2040 MCU/Crystal In: C9.1, U12.20 (XIN), Y3.1
/RP2040 MCU/Crystal Out: R15.1, U12.21 (XOUT)
/RP2040 MCU/QSPI_SCLK: U3.6 (CLK), U12.52 (QSPI_SCLK)
/RP2040 MCU/QSPI_SD0: U3.5 (DI(IO0)), U12.53 (QSPI_SD0)
/RP2040 MCU/QSPI_SD1: U3.2 (DO(IO1)), U12.55 (QSPI_SD1)
/RP2040 MCU/QSPI_SD2: U3.3 (IO2), U12.54 (QSPI_SD2)
/RP2040 MCU/QSPI_SD3: U3.7 (IO3), U12.51 (QSPI_SD3)
/RP2040 MCU/QSPI_SS: U3.1 (~CS), U12.56 (QSPI_SS)
GND: C6.2, C9.2, C10.2, C11.2, C12.2, C13.2, C14.2, C15.2, C16.2, C18.2, C31.2, C32.2, C33.2, C34.2, C35.2, C36.2, C37.2, C38.2, C39.2, C40.2, C41.1, C42.1, J4.4 (ID), J4.5 (GND), J6.6 (VSS), J6.9 (SHIELD), R22.2, U3.4 (GND), U4.2 (GND), U7.6 (GND), U7.8 (GND), U12.19 (TESTEN), U12.26 (RUN), U12.57 (GND), U13.6 (GND), U13.7 (IN-), U14.4 (GND), U14.9 (EP), U15.2 (GND), U16.2 (GND), U16.16 (GND), U16.17 (GND), Y3.2, Y3.4
IMU SCL/SPC: U7.1 (SCL/SPC), U12.30 (GPIO19)
IMU SDA/SDI/SCO: U7.4 (SDA/SDI/SCO), U12.29 (GPIO18)
MicroSD CMD: J6.3 (CMD), U12.2 (GPIO0)
MicroSD Clock: J6.5 (CLK), U12.7 (GPIO5)
MicroSD DAT0: J6.7 (DAT0), U12.3 (GPIO1)
MicroSD DAT1: J6.8 (DAT1), U12.4 (GPIO2)
MicroSD DAT2: J6.1 (DAT2), U12.5 (GPIO3)
MicroSD DAT3: J6.2 (DAT3/CD), U12.6 (GPIO4)
unnamed: C10.1, R15.2, Y3.3
unnamed: C15.1, JP2.1 (A), L2.1
unnamed: C16.1, JP2.2 (B), L2.2, U16.1 (ANT)
unnamed: C13.1, U7.5 (C1)
unnamed: R17.2, U12.46 (USB_DM)
unnamed: R16.2, U12.47 (USB_DP)
unnamed: R22.1, U14.7 (A0)
Power Monitor Input: C6.1, C12.1, C14.1, C18.1, C31.1, C32.1, C33.1, C34.1, C35.1, C36.1, C39.1, C41.2, J6.4 (VDD), R2.1, R7.1, R18.1, R19.2, R20.2, R21.2, U3.8 (VCC), U4.3 (VO), U7.2 (CS_XL), U7.3 (CS_MAG), U7.9 (Vdd), U7.10 (Vdd_I/O), U12.1 (IOVDD), U12.10 (IOVDD), U12.22 (IOVDD), U12.33 (IOVDD), U12.42 (IOVDD), U12.43 (ADC_AVDD), U12.44 (VREG_IN), U12.48 (USB_VDD), U12.49 (IOVDD), U13.5 (VS), U13.8 (IN+), U14.8 (V+), U15.8 (VCC), U16.9 (3.3V)
Power Monitor SCL: R18.2, U12.9 (GPIO7), U13.1 (A1), U13.4 (SCL)
Power Monitor SDA: R7.2, U12.8 (GPIO6), U13.2 (A0), U13.3 (SDA)
RF DIO4: U12.11 (GPIO8), U16.4 (DI/O4)
RF MISO: U12.12 (GPIO9), U16.10 (MISO)
RF MOSI: U12.13 (GPIO10), U16.11 (MOSI)
RF NSS: U12.15 (GPIO12), U16.13 (NSS)
RF Reset: U12.16 (GPIO13), U16.14 (RESET)
RF SCK: U12.14 (GPIO11), U16.12 (SCK)
SET0: U12.27 (GPIO16), U15.4 (SET0)
SET1: U12.18 (GPIO15), U15.5 (SET1)
SET2: U12.17 (GPIO14), U15.6 (SET2)
Temp Alert: R19.1, R20.1, R21.1, U12.31 (GPIO20), U12.32 (GPIO21), U12.34 (GPIO22), U14.1 (SDA), U14.2 (SCL), U14.3 (ALERT), U14.5 (A2), U14.6 (A1)
WDI: U12.28 (GPIO17), U15.1 (WDI)
WDO: R2.2, U15.7 (~WDO)
